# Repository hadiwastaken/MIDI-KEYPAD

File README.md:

# MIDI KEYPAD

** what is MIDI-KEYPAD**
*  So basically a midi-keypad is uesd to control music and different functions in audio software and i am building it for learning PCB designs and electronics bcuz i have interest in building stuff.

 **features**
 * piano style touch keys
 * slider control
 * esp32 microcontroller
 * RGB LEDS
 * rotatry encoder
 * switches

**design**
i am attaching my schematic and pcb image in the readme

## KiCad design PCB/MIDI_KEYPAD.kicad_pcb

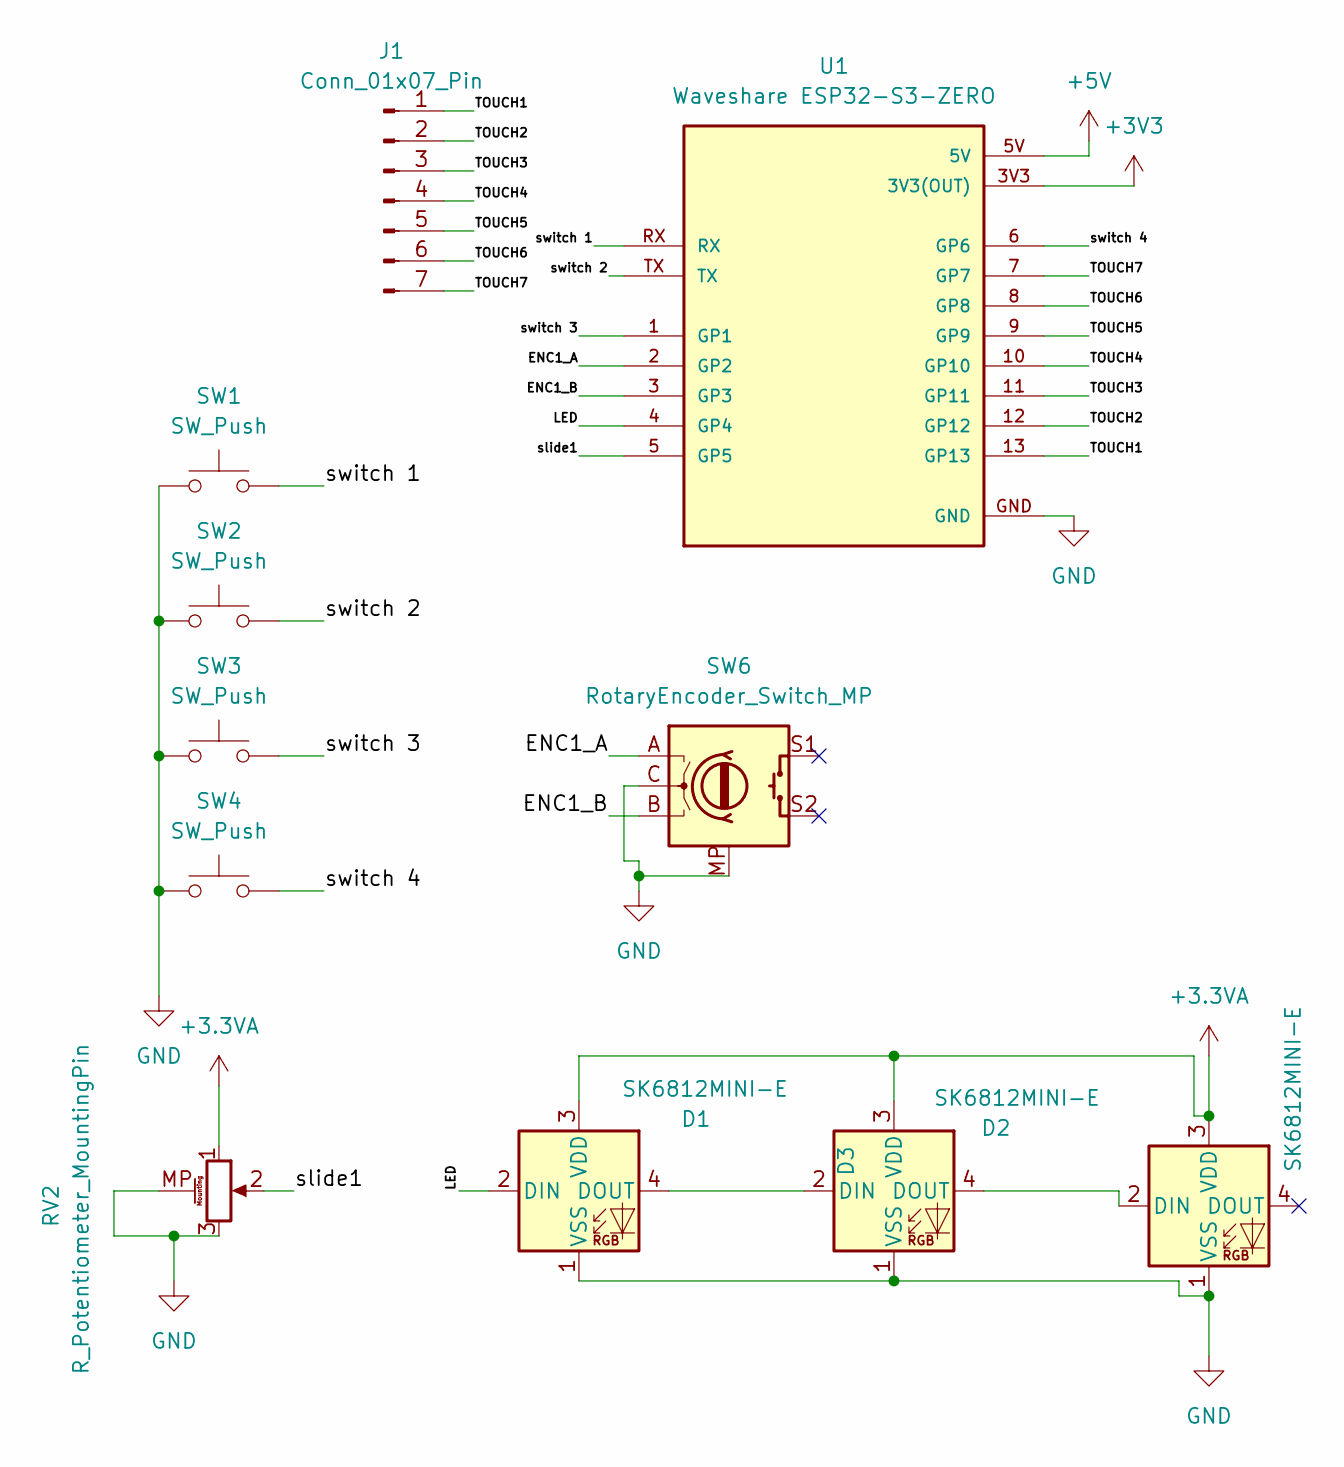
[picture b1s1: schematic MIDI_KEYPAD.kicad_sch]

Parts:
D1, D2, D3: SK6812MINI-E; LED_SK6812MINI-E_3.2x2.8mm_P1.5mm_ReverseMount
J1: Conn_01x07_Pin; capacitive keys 2
RV2: R_Potentiometer_MountingPin; Potentiometer_Bourns_PTA1543_Single_Slide
SW1, SW2, SW3, SW4: SW_Push; Kailh Choc Low-Profile Switches
SW6: RotaryEncoder_Switch_MP; RotaryEncoder_Alps_EC11E-Switch_Vertical_H20mm
U1: Waveshare ESP32-S3-ZERO; Waveshare ESP32-S3-Zero; PARTREV NA

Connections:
+3.3VA: D1.3 (VDD), D2.3 (VDD), D3.3 (VDD), RV2.1
+3V3: U1.3V3 (3V3(OUT))
+5V: U1.5V
/ENC1_A: SW6.A, U1.2 (GP2)
/ENC1_B: SW6.B, U1.3 (GP3)
/LED: D1.2 (DIN), U1.4 (GP4)
/TOUCH1: J1.1, U1.13 (GP13)
/TOUCH2: J1.2, U1.12 (GP12)
/TOUCH3: J1.3, U1.11 (GP11)
/TOUCH4: J1.4, U1.10 (GP10)
/TOUCH5: J1.5, U1.9 (GP9)
/TOUCH6: J1.6, U1.8 (GP8)
/TOUCH7: J1.7, U1.7 (GP7)
/slide1: RV2.2, U1.5 (GP5)
/switch 1: SW1.2, U1.RX
/switch 2: SW2.2, U1.TX
/switch 3: SW3.2, U1.1 (GP1)
/switch 4: SW4.2, U1.6 (GP6)
GND: D1.1 (VSS), D2.1 (VSS), D3.1 (VSS), RV2.3, RV2.MP (MountPin), SW1.1, SW2.1, SW3.1, SW4.1, SW6.C, SW6.MP, U1.GND
unnamed: D1.4 (DOUT), D2.2 (DIN)
unnamed: D2.4 (DOUT), D3.2 (DIN)

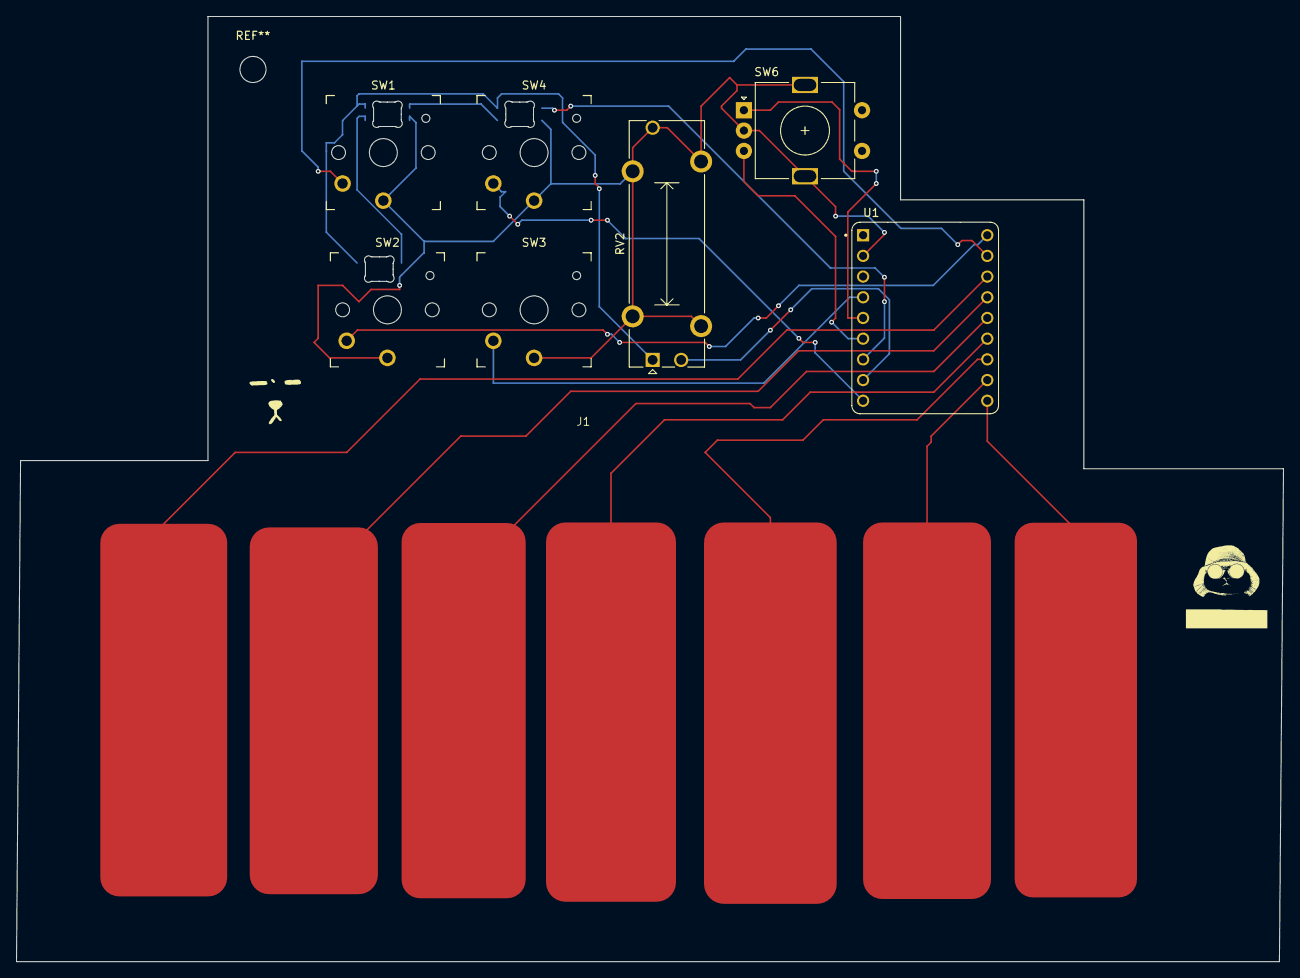
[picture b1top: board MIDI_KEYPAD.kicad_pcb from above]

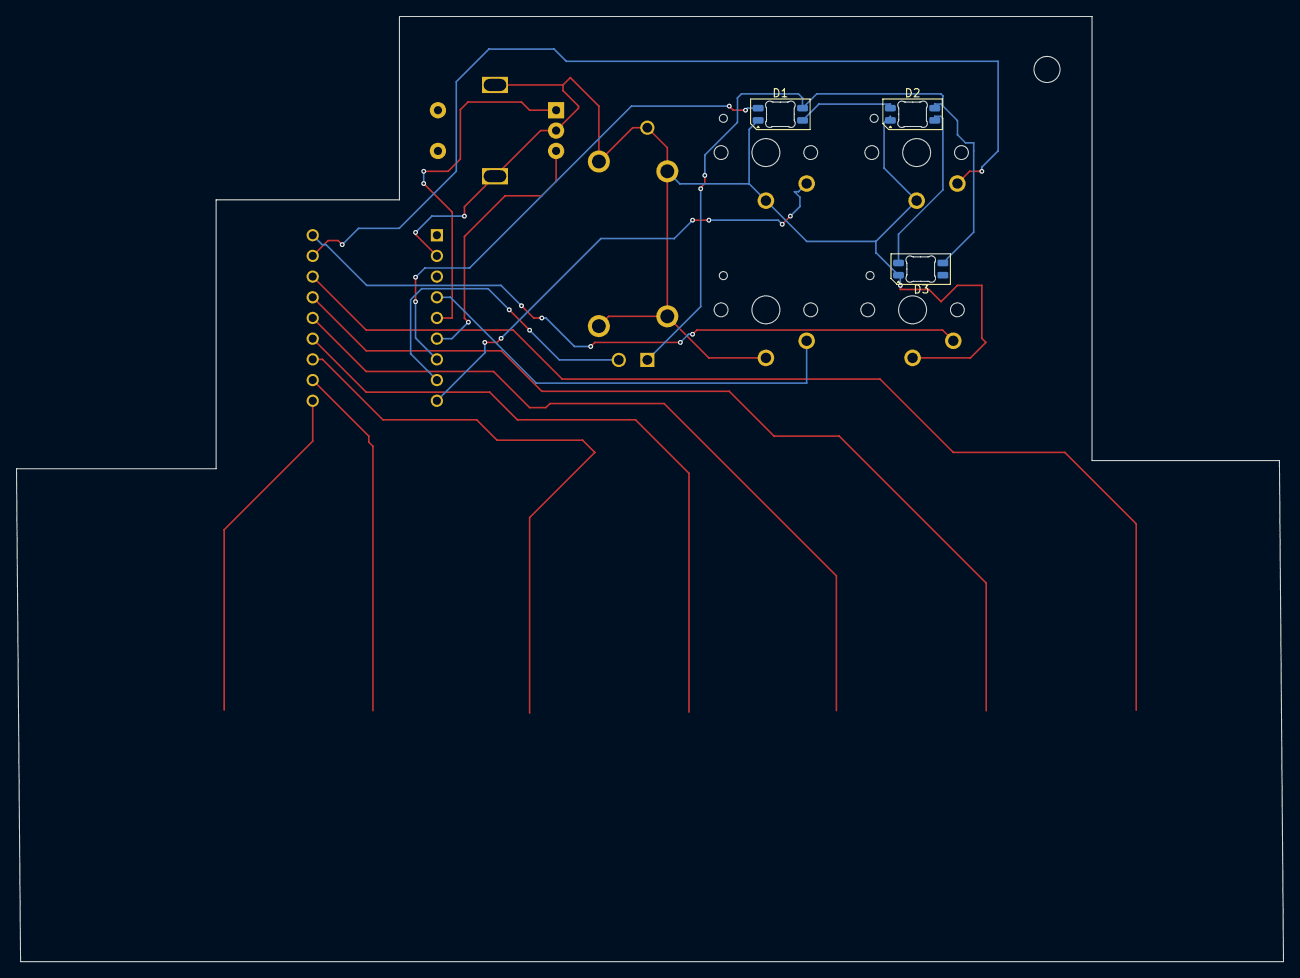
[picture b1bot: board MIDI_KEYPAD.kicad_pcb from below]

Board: 2 copper layers, 155.5 x 116.0 mm, 13 parts (3 on the bottom side), 19 nets.

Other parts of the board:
-: LOGO
`: LOGO

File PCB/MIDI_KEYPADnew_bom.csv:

Designator,Footprint,Quantity,Value,LCSC Part #
"D1, D2, D3",LED_SK6812MINI-E_3.2x2.8mm_P1.5mm_ReverseMount,3,SK6812MINI-E,
J1,capacitive keys 2,1,Conn_01x07_Pin,
RV2,Potentiometer_Bourns_PTA1543_Single_Slide,1,R_Potentiometer_MountingPin,
"SW1, SW2, SW3, SW4",Kailh Choc Low-Profile Switches,4,SW_Push,
SW6,RotaryEncoder_Alps_EC11E-Switch_Vertical_H20mm,1,RotaryEncoder_Switch_MP,
U1,Waveshare ESP32-S3-Zero,1,Waveshare ESP32-S3-ZERO,
